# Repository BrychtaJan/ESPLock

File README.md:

# Project Title

🔒 Hi, I'm Jan Brychta, and this is my project that combines ESP32 and it's WiFi ability and RFID reader RC522 to create a remote RFID lock 🔒

## Authors

- [@Omikron](https://github.com/BrychtaJan)

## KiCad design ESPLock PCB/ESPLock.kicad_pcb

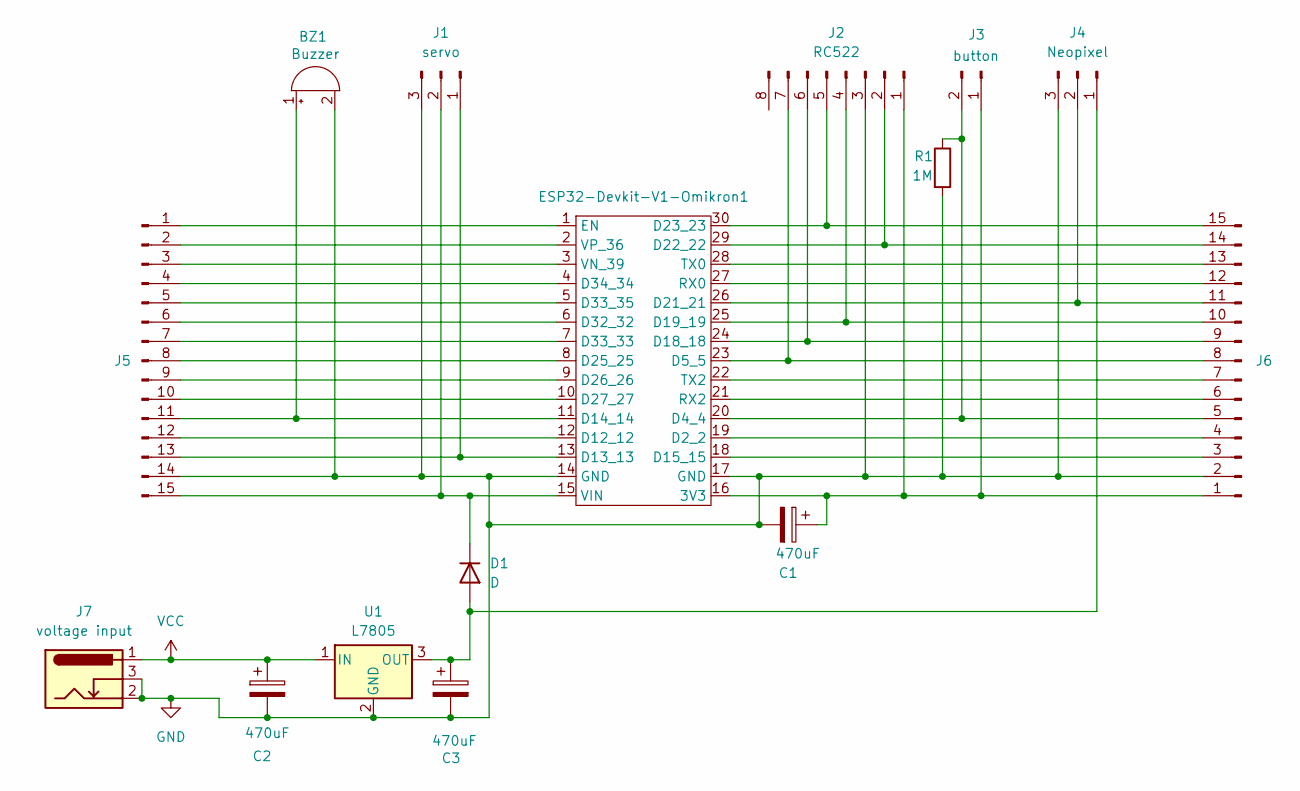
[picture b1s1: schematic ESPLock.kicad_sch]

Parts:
BZ1: Buzzer; Buzzer_12x9.5RM7.6
C1, C2, C3: 470uF; CP_Radial_D8.0mm_P3.50mm
D1: D; D_A-405_P7.62mm_Horizontal
ESP32-Devkit-V1-Omikron1: ESP32-Devkit-V1-Omikron
J1: servo; PinHeader_1x03_P2.54mm_Vertical
J2: RC522; PinHeader_1x08_P2.54mm_Vertical
J3: button; PinSocket_1x02_P2.54mm_Vertical
J4: Neopixel; PinSocket_1x03_P2.54mm_Vertical
J5, J6: Conn_01x15_Pin; PinHeader_1x15_P2.54mm_Vertical
J7: voltage input; BarrelJack_GCT_DCJ200-10-A_Horizontal
R1: 1M; R_Axial_DIN0309_L9.0mm_D3.2mm_P12.70mm_Horizontal
U1: L7805; TO-220F-3_Horizontal_TabDown

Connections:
GND: BZ1.2 (-), C1.2, C2.2, C3.2, ESP32-Devkit-V1-Omikron1.14 (GND), ESP32-Devkit-V1-Omikron1.17 (GND), J1.3, J2.3, J4.3, J5.14, J6.2, J7.2, J7.3, R1.2, U1.2 (GND)
unnamed: BZ1.1 (+), ESP32-Devkit-V1-Omikron1.11 (D14_14), J5.11
unnamed: C3.1, D1.2 (A), J4.1, U1.3 (OUT)
unnamed: D1.1 (K), ESP32-Devkit-V1-Omikron1.15 (VIN), J1.2, J5.15
unnamed: C1.1, ESP32-Devkit-V1-Omikron1.16 (3V3), J2.1, J3.1, J6.1
unnamed: ESP32-Devkit-V1-Omikron1.19 (D2_2), J6.4
unnamed: ESP32-Devkit-V1-Omikron1.20 (D4_4), J3.2, J6.5, R1.1
unnamed: ESP32-Devkit-V1-Omikron1.23 (D5_5), J2.7, J6.8
unnamed: ESP32-Devkit-V1-Omikron1.12 (D12_12), J5.12
unnamed: ESP32-Devkit-V1-Omikron1.13 (D13_13), J1.1, J5.13
unnamed: ESP32-Devkit-V1-Omikron1.18 (D15_15), J6.3
unnamed: ESP32-Devkit-V1-Omikron1.24 (D18_18), J2.6, J6.9
unnamed: ESP32-Devkit-V1-Omikron1.25 (D19_19), J2.4, J6.10
unnamed: ESP32-Devkit-V1-Omikron1.26 (D21_21), J4.2, J6.11
unnamed: ESP32-Devkit-V1-Omikron1.29 (D22_22), J2.2, J6.14
unnamed: ESP32-Devkit-V1-Omikron1.30 (D23_23), J2.5, J6.15
unnamed: ESP32-Devkit-V1-Omikron1.8 (D25_25), J5.8
unnamed: ESP32-Devkit-V1-Omikron1.9 (D26_26), J5.9
unnamed: ESP32-Devkit-V1-Omikron1.10 (D27_27), J5.10
unnamed: ESP32-Devkit-V1-Omikron1.6 (D32_32), J5.6
unnamed: ESP32-Devkit-V1-Omikron1.7 (D33_33), J5.7
unnamed: ESP32-Devkit-V1-Omikron1.5 (D33_35), J5.5
unnamed: ESP32-Devkit-V1-Omikron1.4 (D34_34), J5.4
unnamed: ESP32-Devkit-V1-Omikron1.1 (EN), J5.1
unnamed: ESP32-Devkit-V1-Omikron1.27 (RX0), J6.12
unnamed: ESP32-Devkit-V1-Omikron1.21 (RX2), J6.6
unnamed: ESP32-Devkit-V1-Omikron1.28 (TX0), J6.13
unnamed: ESP32-Devkit-V1-Omikron1.22 (TX2), J6.7
unnamed: ESP32-Devkit-V1-Omikron1.3 (VN_39), J5.3
unnamed: ESP32-Devkit-V1-Omikron1.2 (VP_36), J5.2
VCC: C2.1, J7.1, U1.1 (IN)

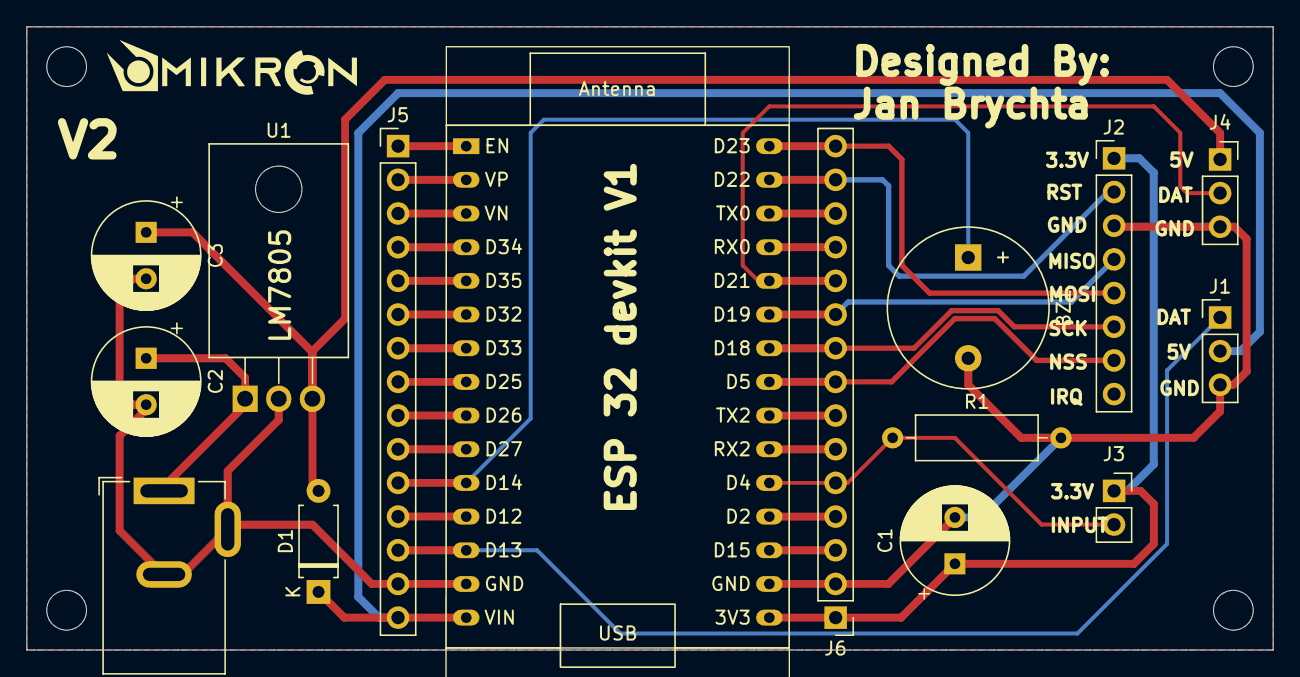
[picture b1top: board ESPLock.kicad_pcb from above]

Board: 2 copper layers, 94.0 x 47.0 mm, 15 parts (0 on the bottom side), 31 nets.

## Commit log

2025-06-17 Release V1.0
    This is the first official Release of ESPLock
